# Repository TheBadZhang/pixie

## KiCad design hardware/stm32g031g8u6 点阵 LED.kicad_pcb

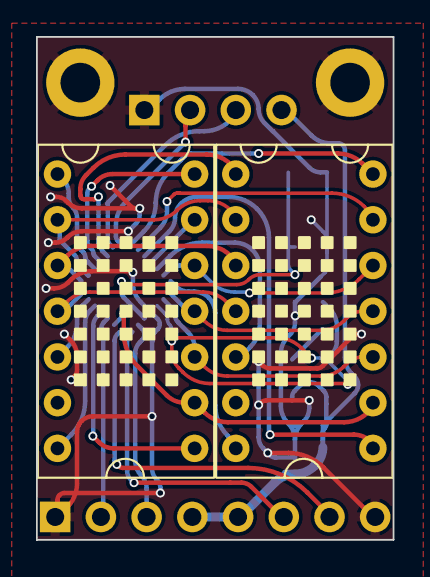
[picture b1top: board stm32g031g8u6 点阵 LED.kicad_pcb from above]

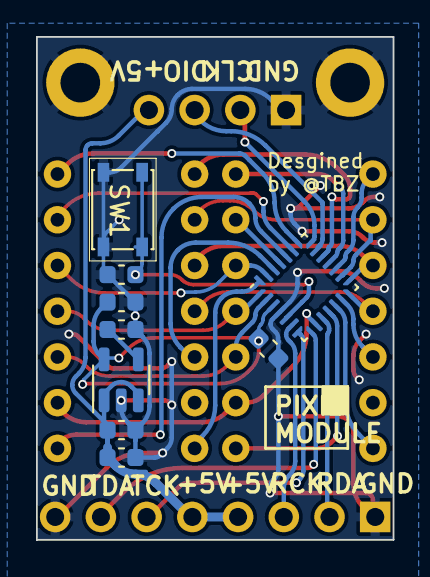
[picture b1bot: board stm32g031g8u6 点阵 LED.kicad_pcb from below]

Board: 2 copper layers, 19.8 x 27.9 mm, 15 parts (9 on the bottom side), 30 nets.

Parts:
C2: C; C_0603_1608Metric
C3, C12: 0.1uF; C_0603_1608Metric
C11, C14: 4.7uF; C_0603_1608Metric
C13: 22nF; C_0603_1608Metric
H3, H4: MountingHole_Pad; MountingHole_2.2mm_M2_DIN965_Pad
J1: Conn_01x04_Pin; PinHeader_1x04_P2.54mm_Vertical
J4: Conn_01x08_Pin; PinHeader_1x08_P2.54mm_Vertical
SW1: SW_Push; KEY-SMD_4P-L4.2-W3.4-P2.15-LS4.5-TL
U1: STM32G031G8Ux; QFN-28_4x4mm_P0.5mm
U2, U3: LTP-305
U5: RT9193-33GB; SOT-23-5

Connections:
+3V3: C3.1, C14.2, U1.3 (VDD), U5.5 (Vout)
+5V: C11.1, C12.1, J1.4, J4.4, J4.5, U5.1 (Vin), U5.3 (EN)
/LTP1.C1: U1.13 (PA7), U2.5 (C1)
/LTP1.C2: U1.17 (PC6), U2.1 (C2)
/LTP1.C3: U1.11 (PA5), U2.8 (C3)
/LTP1.C4: U1.18 (PA11/PA9), U2.14 (C4)
/LTP1.C5: U1.25 (PB5), U2.13 (C5)
/LTP1_POINT: U1.12 (PA6), U2.7 (POINT)
/LTP2.C1: U1.26 (PB6), U3.5 (C1)
/LTP2.C2: U1.19 (PA12/PA10), U3.1 (C2)
/LTP2.C3: U1.24 (PB4), U3.8 (C3)
/LTP2.C4: U1.22 (PA15), U3.14 (C4)
/LTP2.C5: U1.23 (PB3), U3.13 (C5)
/LTP2_POINT: U1.28 (PB8), U3.7 (POINT)
/NRST: C2.2, SW1.1, U1.5 (PF2)
/R1: U1.16 (PA8), U2.2 (R1), U3.2 (R1)
/R2: U1.27 (PB7), U2.12 (R2), U3.12 (R2)
/R3: U1.15 (PB1), U2.3 (R3), U3.3 (R3)
/R4: U1.14 (PB0), U2.4 (R4), U3.4 (R4)
/R5: U1.1 (PC14), U2.11 (R5), U3.11 (R5)
/R6: U1.2 (PC15), U2.10 (R6), U3.10 (R6)
/R7: U1.9 (PA3), U2.9 (R7), U3.9 (R7)
/SYS.SWCLK: J1.2, U1.21 (PA14)
/SYS.SWDIO: J1.3, U1.20 (PA13)
/receive_clk: J4.3, U1.6 (PA0)
/receive_sda: J4.2, U1.10 (PA4)
/transmit_clk: J4.6, U1.7 (PA1)
/transmit_sda: J4.7, U1.8 (PA2)
GND: C2.1, C3.2, C11.2, C12.2, C13.2, C14.1, H3.1, H4.1, J1.1, J4.1, J4.8, SW1.2, U1.4 (VSS), U5.2 (GND)
unnamed: C13.1, U5.4 (BP)

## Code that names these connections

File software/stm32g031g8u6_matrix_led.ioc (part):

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Mcu.Name=STM32G031G(4-6-8)Ux
Mcu.Package=UFQFPN28
Mcu.UserName=STM32G031G8Ux
PA0.Mode=RX_Only_Simplex_Unidirect_Slave
PA0.Signal=SPI2_SCK
PA1.Mode=TX_Only_Simplex_Unidirect_Master
PA1.Signal=SPI1_SCK
PA11\ [PA9].GPIOParameters=GPIO_Label
PA11\ [PA9].GPIO_Label=LTP1C4
PA11\ [PA9].Signal=GPIO_Output
PA12\ [PA10].GPIOParameters=GPIO_Label
PA12\ [PA10].GPIO_Label=LTP2C2
PA12\ [PA10].Signal=GPIO_Output
PA13.Mode=Serial_Wire
PA13.Signal=SYS_SWDIO
PA14-BOOT0.Mode=Serial_Wire
PA14-BOOT0.Signal=SYS_SWCLK
PA15.GPIOParameters=GPIO_Label
PA15.GPIO_Label=LTP2C4
PA15.Signal=GPIO_Output
PA2.Mode=TX_Only_Simplex_Unidirect_Master
PA2.Signal=SPI1_MOSI
PA3.GPIOParameters=GPIO_Label
PA3.GPIO_Label=R7
PA3.Signal=GPIO_Output
PA4.Mode=RX_Only_Simplex_Unidirect_Slave
PA4.Signal=SPI2_MOSI
PA5.GPIOParameters=GPIO_Label
PA5.GPIO_Label=LTP1C3
PA5.Signal=GPIO_Output
PA6.GPIOParameters=GPIO_Label
PA6.GPIO_Label=LTP1P
PA6.Signal=GPIO_Output
PA7.GPIOParameters=GPIO_Label
PA7.GPIO_Label=LTP1C1
PA7.Signal=GPIO_Output
PA8.GPIOParameters=GPIO_Label
PA8.GPIO_Label=R1
PA8.Signal=GPIO_Output
PB0.GPIOParameters=GPIO_Label
PB0.GPIO_Label=R4
PB0.Signal=GPIO_Output
PB1.GPIOParameters=GPIO_Label
PB1.GPIO_Label=R3
PB1.Signal=GPIO_Output
PB3.GPIOParameters=GPIO_Label
PB3.GPIO_Label=LTP2C5
PB3.Signal=GPIO_Output
PB4.GPIOParameters=GPIO_Label
PB4.GPIO_Label=LTP2C3
PB4.Signal=GPIO_Output
PB5.GPIOParameters=GPIO_Label
PB5.GPIO_Label=LTP1C5
PB5.Signal=GPIO_Output
PB6.GPIOParameters=GPIO_Label
PB6.GPIO_Label=LTP2C1
PB6.Signal=GPIO_Output
PB7.GPIOParameters=GPIO_Label
PB7.GPIO_Label=R2
PB7.Signal=GPIO_Output
PB8.GPIOParameters=GPIO_Label
PB8.GPIO_Label=LTP2P
PB8.Signal=GPIO_Output
PC14-OSC32_IN\ (PC14).GPIOParameters=GPIO_Label
PC14-OSC32_IN\ (PC14).GPIO_Label=R5
PC14-OSC32_IN\ (PC14).Signal=GPIO_Output
PC15-OSC32_OUT\ (PC15).GPIOParameters=GPIO_Label
PC15-OSC32_OUT\ (PC15).GPIO_Label=R6
PC15-OSC32_OUT\ (PC15).Signal=GPIO_Output
PC6.GPIOParameters=GPIO_Label
PC6.GPIO_Label=LTP1C2
PC6.Signal=GPIO_Output
RCC.HSE_VALUE=8000000
RCC.SYSCLKFreq_VALUE=64000000
RCC.SYSCLKSource=RCC_SYSCLKSOURCE_PLLCLK
board=custom

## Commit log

2023-08-26 硬件电路
2023-08-26 软件代码
2023-08-26 尝试对每个像素进行pwm控制
2023-08-26 一些简单的动画，不过不应该出现在这里才对，这个32只是一个驱动器
2024-01-20 忘记了是什么修改了
